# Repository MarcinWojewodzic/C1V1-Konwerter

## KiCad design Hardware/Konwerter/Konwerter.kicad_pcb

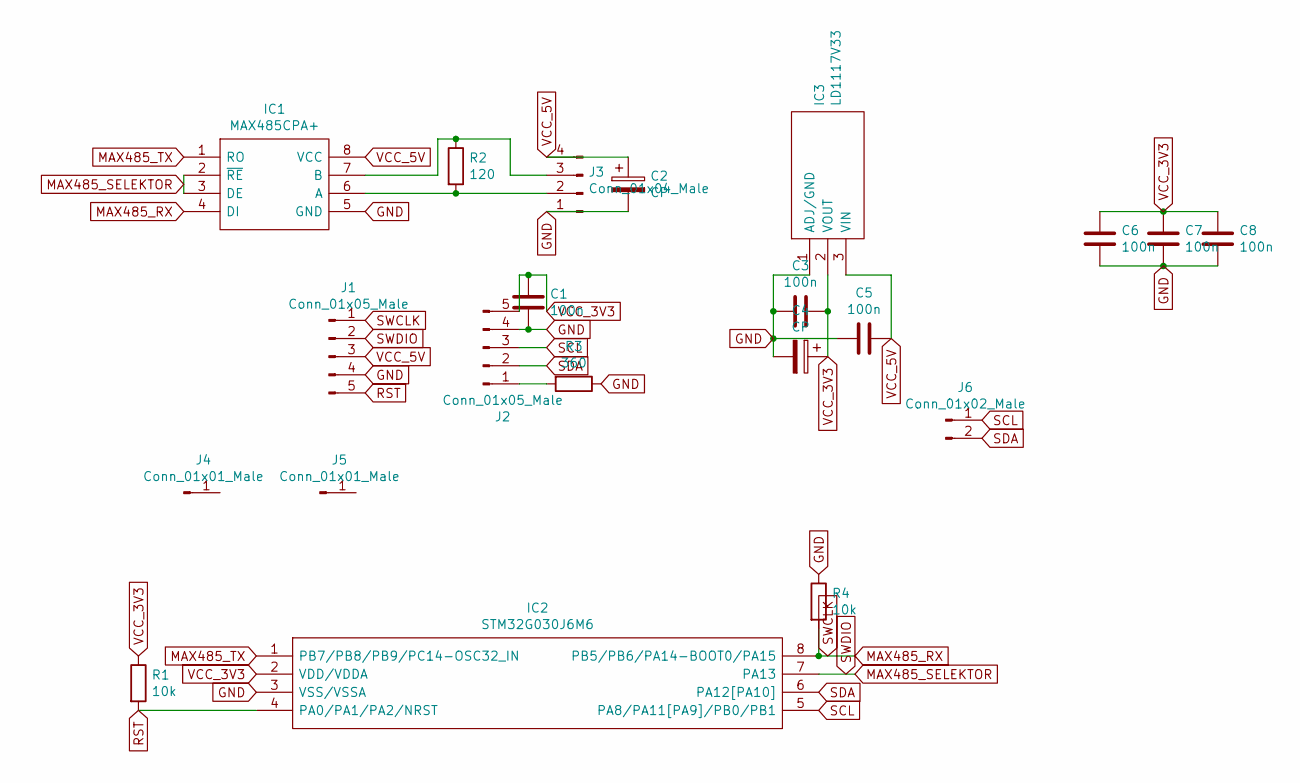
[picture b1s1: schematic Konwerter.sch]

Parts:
C1, C3, C5, C6, C7, C8: 100n; C_1206_3216Metric_Pad1.33x1.80mm_HandSolder
C2, C4: CP; CP_Elec_5x5.4
IC1: MAX485CPA+; DIP794W56P254L938H457Q8N; Manufacturer_Part_Number MAX485CPA+; Mouser Part Number 700-MAX485CPA
IC2: STM32G030J6M6; SOIC127P600X175-8N; Manufacturer_Part_Number STM32G030J6M6; Mouser Part Number 511-STM32G030J6M6
IC3: LD1117V33; TO255P460X1020X2008-3P; Manufacturer_Part_Number LD1117V33; Mouser Part Number 511-LD1117V33
J1, J2: Conn_01x05_Male; PinHeader_1x05_P2.54mm_Vertical
J3: Conn_01x04_Male; TerminalBlock_bornier-4_P5.08mm
J4, J5: Conn_01x01_Male; PinHeader_1x01_P2.54mm_Vertical
J6: Conn_01x02_Male; PinHeader_1x02_P2.54mm_Vertical
R1, R4: 10k; R_1206_3216Metric_Pad1.30x1.75mm_HandSolder
R2: 120; R_1206_3216Metric_Pad1.30x1.75mm_HandSolder
R3: 360; R_1206_3216Metric_Pad1.30x1.75mm_HandSolder

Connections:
GND: C1.2, C2.2, C3.1, C4.2, C5.1, C6.2, C7.2, C8.2, IC1.5 (GND), IC2.3 (VSS/VSSA), IC3.1 (ADJ/GND), J1.4, J2.4, J3.1, R3.1, R4.1
MAX485_RX: IC1.4 (DI), IC2.8 (PB5/PB6/PA14-BOOT0/PA15), J1.1, R4.2
MAX485_SELEKTOR: IC1.2 (~RE), IC1.3 (DE), IC2.7 (PA13), J1.2
MAX485_TX: IC1.1 (RO), IC2.1 (PB7/PB8/PB9/PC14-OSC32_IN)
unnamed: IC1.6 (A), J3.2, R2.2
unnamed: IC1.7 (B), J3.3, R2.1
unnamed: J2.1, R3.2
RST: IC2.4 (PA0/PA1/PA2/NRST), J1.5, R1.2
SCL: IC2.5 (PA8/PA11[PA9]/PB0/PB1), J2.3, J6.1
SDA: IC2.6 (PA12[PA10]), J2.2, J6.2
VCC_3V3: C1.1, C3.2, C4.1, C6.1, C7.1, C8.1, IC2.2 (VDD/VDDA), IC3.2 (VOUT), J2.5, R1.1
VCC_5V: C2.1, C5.2, IC1.8 (VCC), IC3.3 (VIN), J1.3, J3.4

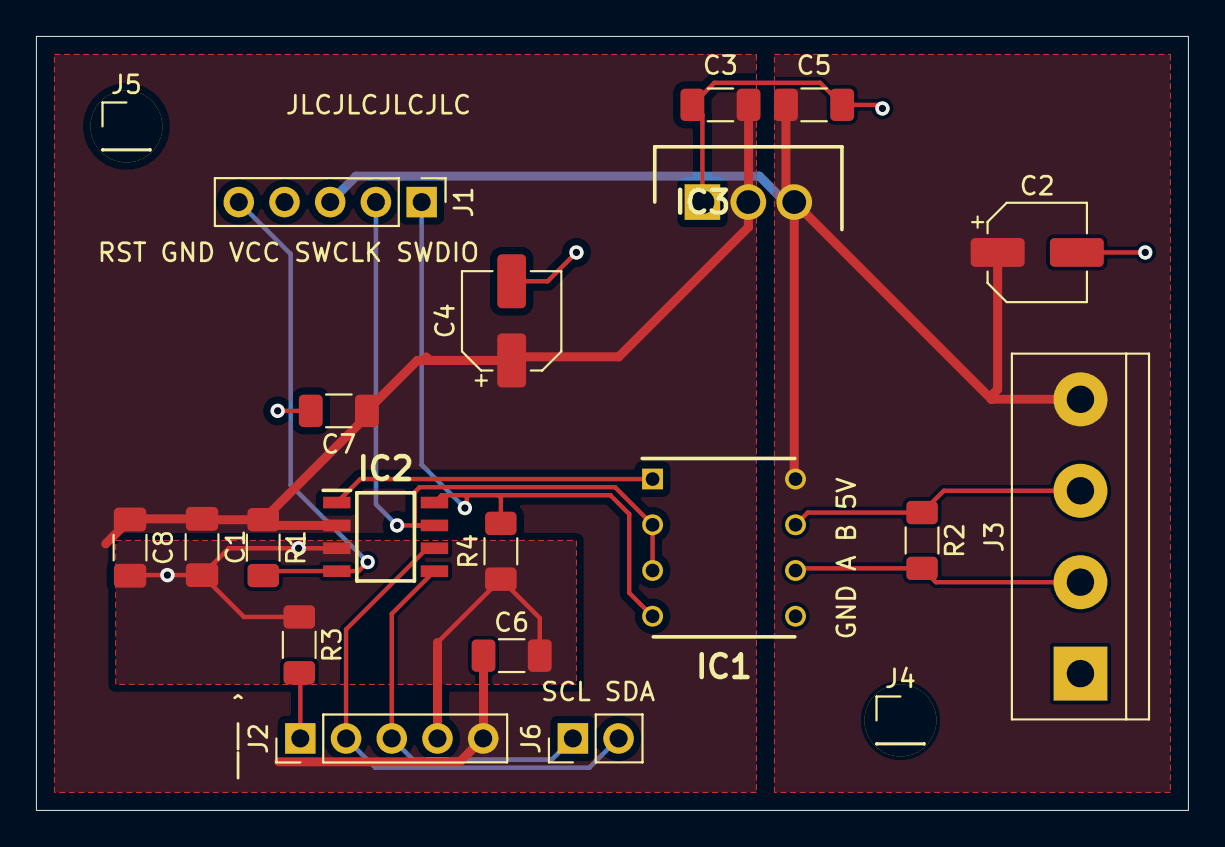
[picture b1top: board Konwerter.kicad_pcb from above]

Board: 2 copper layers, 64.0 x 43.0 mm, 21 parts (0 on the bottom side), 12 nets.

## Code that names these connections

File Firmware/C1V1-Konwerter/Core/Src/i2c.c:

/* USER CODE BEGIN Header */
/**
  ******************************************************************************
  * @file    i2c.c
  * @brief   This file provides code for the configuration
  *          of the I2C instances.
  ******************************************************************************
  * @attention
  *
  * Copyright (c) 2022 STMicroelectronics.
  * All rights reserved.
  *
  * This software is licensed under terms that can be found in the LICENSE file
  * in the root directory of this software component.
  * If no LICENSE file comes with this software, it is provided AS-IS.
  *
  ******************************************************************************
  */
/* USER CODE END Header */
/* Includes ------------------------------------------------------------------*/
#include "i2c.h"

/* USER CODE BEGIN 0 */

/* USER CODE END 0 */

I2C_HandleTypeDef hi2c2;

/* I2C2 init function */
void MX_I2C2_Init(void)
{

  /* USER CODE BEGIN I2C2_Init 0 */

  /* USER CODE END I2C2_Init 0 */

  /* USER CODE BEGIN I2C2_Init 1 */

  /* USER CODE END I2C2_Init 1 */
  hi2c2.Instance = I2C2;
  hi2c2.Init.Timing = 0x2000090E;
  hi2c2.Init.OwnAddress1 = 0;
  hi2c2.Init.AddressingMode = I2C_ADDRESSINGMODE_7BIT;
  hi2c2.Init.DualAddressMode = I2C_DUALADDRESS_DISABLE;
  hi2c2.Init.OwnAddress2 = 0;
  hi2c2.Init.OwnAddress2Masks = I2C_OA2_NOMASK;
  hi2c2.Init.GeneralCallMode = I2C_GENERALCALL_DISABLE;
  hi2c2.Init.NoStretchMode = I2C_NOSTRETCH_DISABLE;
  if (HAL_I2C_Init(&hi2c2) != HAL_OK)
  {
    Error_Handler();
  }

  /** Configure Analogue filter
  */
  if (HAL_I2CEx_ConfigAnalogFilter(&hi2c2, I2C_ANALOGFILTER_ENABLE) != HAL_OK)
  {
    Error_Handler();
  }

  /** Configure Digital filter
  */
  if (HAL_I2CEx_ConfigDigitalFilter(&hi2c2, 0) != HAL_OK)
  {
    Error_Handler();
  }
  /* USER CODE BEGIN I2C2_Init 2 */

  /* USER CODE END I2C2_Init 2 */

}

void HAL_I2C_MspInit(I2C_HandleTypeDef* i2cHandle)
{

  GPIO_InitTypeDef GPIO_InitStruct = {0};
  if(i2cHandle->Instance==I2C2)
  {
  /* USER CODE BEGIN I2C2_MspInit 0 */

  /* USER CODE END I2C2_MspInit 0 */

    __HAL_RCC_GPIOA_CLK_ENABLE();
    /**I2C2 GPIO Configuration
    PA11 [PA9]     ------> I2C2_SCL
    PA12 [PA10]     ------> I2C2_SDA
    */
    GPIO_InitStruct.Pin = GPIO_PIN_11|GPIO_PIN_12;
    GPIO_InitStruct.Mode = GPIO_MODE_AF_OD;
    GPIO_InitStruct.Pull = GPIO_NOPULL;
    GPIO_InitStruct.Speed = GPIO_SPEED_FREQ_LOW;
    GPIO_InitStruct.Alternate = GPIO_AF6_I2C2;
    HAL_GPIO_Init(GPIOA, &GPIO_InitStruct);

    /* I2C2 clock enable */
    __HAL_RCC_I2C2_CLK_ENABLE();
  /* USER CODE BEGIN I2C2_MspInit 1 */

  /* USER CODE END I2C2_MspInit 1 */
  }
}

void HAL_I2C_MspDeInit(I2C_HandleTypeDef* i2cHandle)
{

  if(i2cHandle->Instance==I2C2)
  {
  /* USER CODE BEGIN I2C2_MspDeInit 0 */

  /* USER CODE END I2C2_MspDeInit 0 */
    /* Peripheral clock disable */
    __HAL_RCC_I2C2_CLK_DISABLE();

    /**I2C2 GPIO Configuration
    PA11 [PA9]     ------> I2C2_SCL
    PA12 [PA10]     ------> I2C2_SDA
    */
    HAL_GPIO_DeInit(GPIOA, GPIO_PIN_11);

    HAL_GPIO_DeInit(GPIOA, GPIO_PIN_12);

  /* USER CODE BEGIN I2C2_MspDeInit 1 */

  /* USER CODE END I2C2_MspDeInit 1 */
  }
}

/* USER CODE BEGIN 1 */

/* USER CODE END 1 */

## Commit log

2022-08-27 Pierwsze Budowanie Projektu
2022-08-27 Dodano DMA i RTC
2022-08-27 Test Wstępny
2022-08-27 Test Zaliczony
2022-08-31 Dodano potrzebne biblioteki
2022-09-03 Dodano struktury do SM
2022-09-03 no message
2022-09-03 Dodano SM.c
2022-09-03 Dodano pierwsze funkcje so SM
2022-09-03 Przetestowano komunikację po RS485
2022-09-03 Usunięto zbędną biblioekę
2022-09-03 Szkielet SM + podstawowe usypianie
2022-09-04 Dodano obsługę podstawowych komend
2022-09-04 Dodano nowe komendy
2022-10-09 merge
2022-11-05 Przebudowano SM i dodano łączność z C2V1
2022-11-05 Dodano czujnik temperatury procesora
2023-01-15 Ukończono
